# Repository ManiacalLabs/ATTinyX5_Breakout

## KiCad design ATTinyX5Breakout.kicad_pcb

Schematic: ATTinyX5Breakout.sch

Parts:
C1: 0.1uF; AXIAL-5MM
IC1: ATTINY85-P; DIP8
J1: ICSP
P1, P2: CONN_4
P3, P4: HEADER_1

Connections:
GND: C1.2, IC1.4 (GND), J1.6, P1.4, P4.1
MISO: IC1.6 (PB1(MISO/DO/AIN1/OC0B/OC1A/PCINT1)), J1.1, P2.3
MOSI: IC1.5 (PB0(MOSI/DI/SDA/AIN0/OC0A/OC1A/AREF/PCI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), J1.4, P2.4
PB3: IC1.2 (PB3(XTAL1/CLKI/OC1B/ADC3/PCINT3)), P1.2
PB4: IC1.3 (PB4(XTAL2/CLKO/OC1B/ADC2/PCINT4)), P1.3
RST: IC1.1 (PB5(~RESET~/dW/ADC0/PCINT5)), J1.5, P1.1
SCK: IC1.7 (PB2(SCK/USCK/SCL/T0/INT0/ADC1/PCINT2)), J1.3, P2.2
VCC: C1.1, IC1.8 (VCC), J1.2, P2.1, P3.1

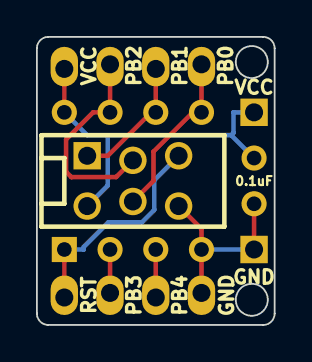
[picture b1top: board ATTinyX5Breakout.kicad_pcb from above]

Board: 2 copper layers, 13.2 x 16.0 mm, 7 parts (1 on the bottom side), 8 nets.

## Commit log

2014-08-03 :circus_tent: Added .gitattributes & .gitignore files
